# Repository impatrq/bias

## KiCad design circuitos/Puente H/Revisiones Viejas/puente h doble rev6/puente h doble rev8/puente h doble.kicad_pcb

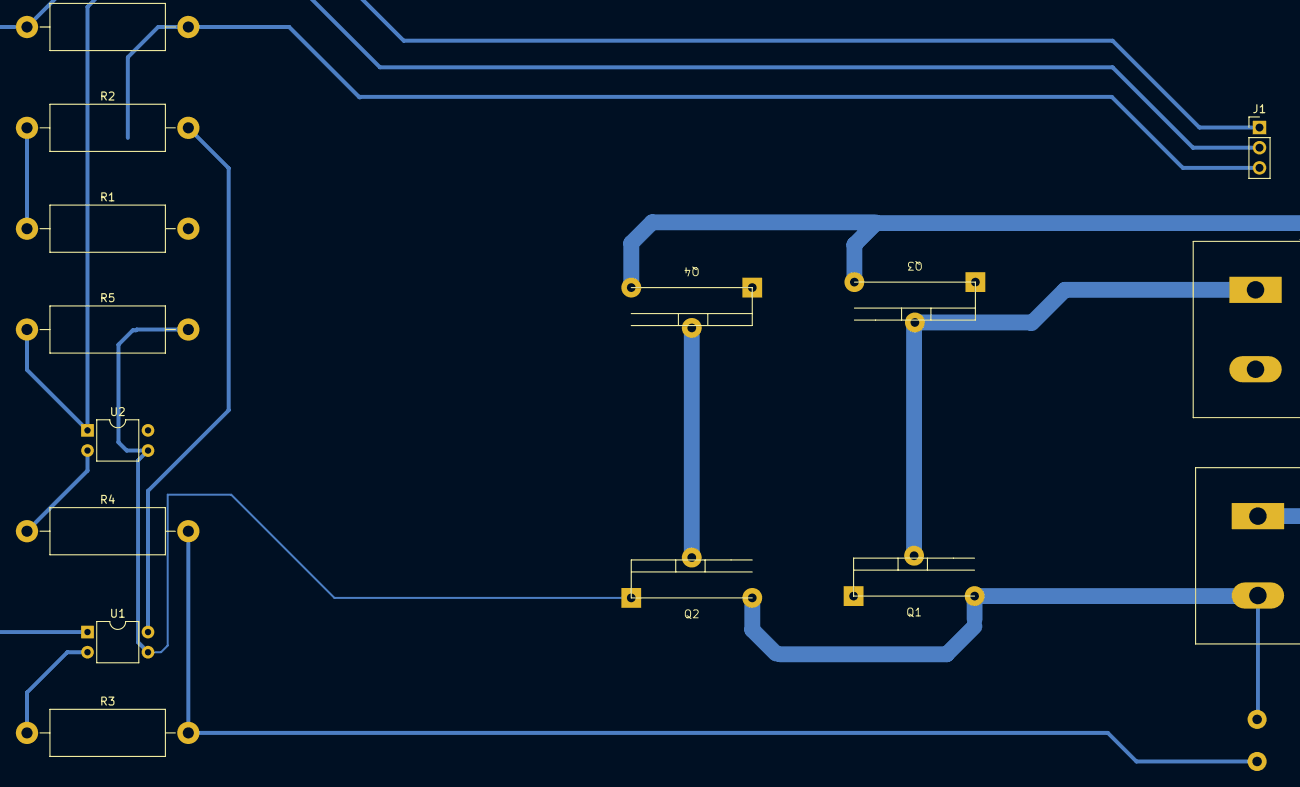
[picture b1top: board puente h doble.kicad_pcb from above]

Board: 2 copper layers, 16 parts (1 on the bottom side), 12 nets.

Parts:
J1: BORNERA X3; PinHeader_1x03_P2.54mm_Vertical
J2: MOTOR; TerminalBlock_Dinkle_DT-55-B01X-02_P10.00mm
J3: Alimentación; TerminalBlock_Dinkle_DT-55-B01X-02_P10.00mm
Q1, Q2: IRLZ44N; to-220 editado
Q3, Q4: IRF4905; to-220 editado
R1, R2: 1k; R_Axial_DIN0614_L14.3mm_D5.7mm_P20.32mm_Horizontal
R3, R4: 100; R_Axial_DIN0614_L14.3mm_D5.7mm_P20.32mm_Horizontal
R5, R6: 4k7; R_Axial_DIN0614_L14.3mm_D5.7mm_P20.32mm_Horizontal
SW2: SW_Push_Open; SW_CW_GPTS203211B
U1, U2: PC817; DIP-4_W7.62mm

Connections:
+12V: R1.1, R2.1
+24V: J3.1, Q3.3 (S), Q4.3 (S)
GND: J1.3, J3.2, Q1.3 (S), Q2.1 (G), Q2.3 (S), R5.2, R6.2, SW2.1 (A), U1.3, U2.3
unnamed: J2.1, Q1.2 (D), Q3.2 (D)
unnamed: J2.2, Q2.2 (D), Q4.2 (D)
unnamed: Q1.1 (G), Q3.1 (G), R2.2, U1.4
unnamed: Q4.1 (G), R1.2, U2.4
unnamed: R3.1, U1.2
unnamed: R4.1, U2.2
unnamed: R3.2, R4.2, SW2.2 (B)
PWM1: J1.1, R6.1, U1.1
PWM2: J1.2, R5.1, U2.1

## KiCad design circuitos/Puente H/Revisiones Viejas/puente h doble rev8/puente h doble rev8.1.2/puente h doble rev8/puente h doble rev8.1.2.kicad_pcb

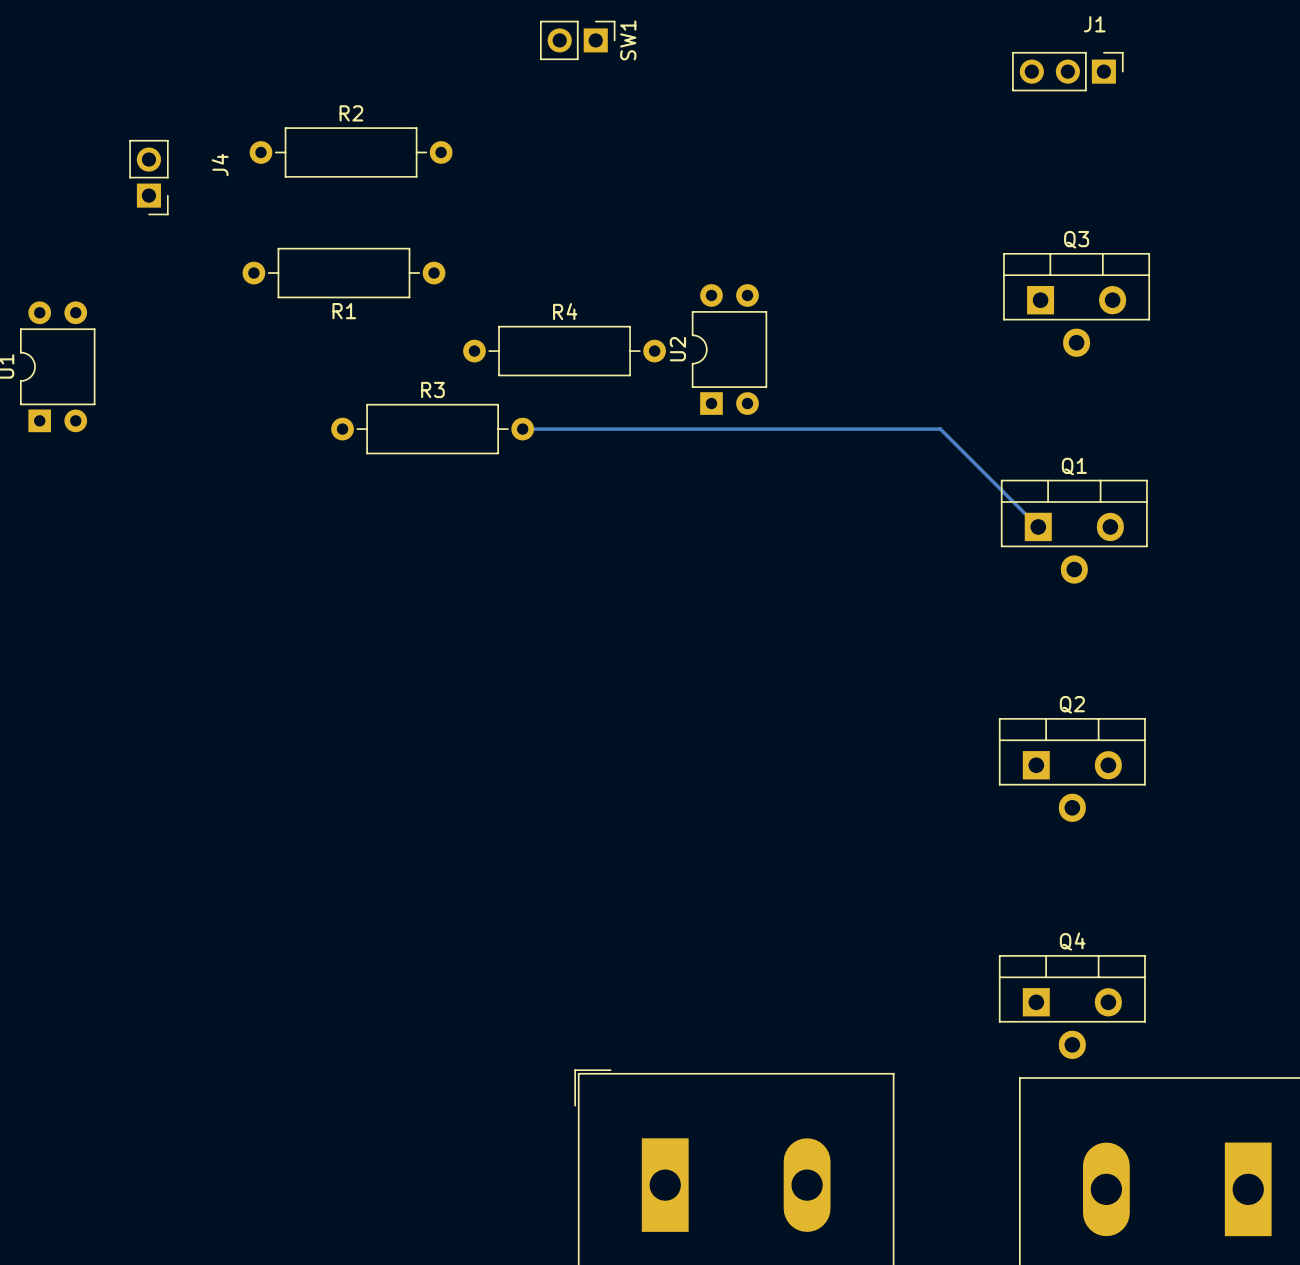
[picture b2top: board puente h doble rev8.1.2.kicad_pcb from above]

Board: 2 copper layers, 15 parts (0 on the bottom side), 13 nets.

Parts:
J1: PWM; PinHeader_1x03_P2.54mm_Vertical
J2: MOTOR; TerminalBlock_Dinkle_DT-55-B01X-02_P10.00mm
J3: 24V Alimentación; TerminalBlock_Dinkle_DT-55-B01X-02_P10.00mm
J4: 15V Alimentación; PinHeader_1x02_P2.54mm_Vertical
Q1, Q3: IRF4905; TO-220-3_Vertical
Q2, Q4: IRLZ44N; TO-220-3_Vertical
R1, R2: 180; R_Axial_DIN0309_L9.0mm_D3.2mm_P12.70mm_Horizontal
R3, R4: 1k; R_Axial_DIN0309_L9.0mm_D3.2mm_P12.70mm_Horizontal
SW1: SW; PinHeader_1x02_P2.54mm_Vertical
U1, U2: PC817; DIP-4_W7.62mm

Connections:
+15V: J4.1, R3.1, R4.1
+24V: J3.1, Q1.3 (S), Q3.3 (S)
GND: J1.3, SW1.1 (A)
GNDPWR: J3.2, J4.2, Q2.3 (S), Q4.3 (S), U1.3, U2.3
unnamed: J2.1, Q1.2 (D), Q2.2 (D)
unnamed: J2.2, Q3.2 (D), Q4.2 (D)
unnamed: Q1.1 (G), Q2.1 (G), R3.2, U1.4
unnamed: Q3.1 (G), Q4.1 (G), R4.2, U2.4
unnamed: R1.2, U1.1
unnamed: R2.1, U2.1
unnamed: SW1.2 (B), U1.2, U2.2
PWM1: J1.1, R1.1
PWM2: J1.2, R2.2
